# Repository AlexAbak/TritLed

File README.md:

# TritLed
Индикатор трита

Документация и обсуждение https://myweek-end.ru/trit/tritled

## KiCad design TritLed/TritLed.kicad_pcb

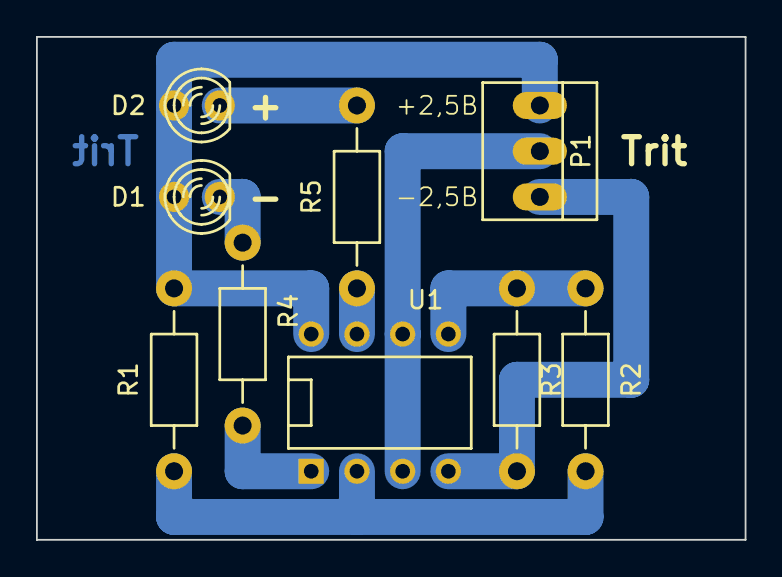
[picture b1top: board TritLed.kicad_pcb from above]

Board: 2 copper layers, 39.4 x 27.9 mm, 9 parts (0 on the bottom side), 9 nets.

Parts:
D1: -; LED-3MM
D2: +; LED-3MM
P1: Power&In; PINHEAD1-3
R1, R2, R3: 4.7KΩ; Resistor_Horizontal_RM10mm
R4, R5: 220Ω; Resistor_Horizontal_RM10mm
U1: LM393; DIP-8__300

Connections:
unnamed: D1.1, D2.1, P1.1, R1.1, U1.8
unnamed: D1.2, R4.1
unnamed: D2.2, R5.1
unnamed: P1.2, U1.3, U1.6
unnamed: P1.3, R3.2, U1.4
unnamed: R1.2, R2.1, U1.2
unnamed: R2.2, R3.1, U1.5
unnamed: R4.2, U1.1
unnamed: R5.2, U1.7

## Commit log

2015-04-26 Заливка схемы
2015-04-26 Экспорт изображений
2015-04-27 Изображения
